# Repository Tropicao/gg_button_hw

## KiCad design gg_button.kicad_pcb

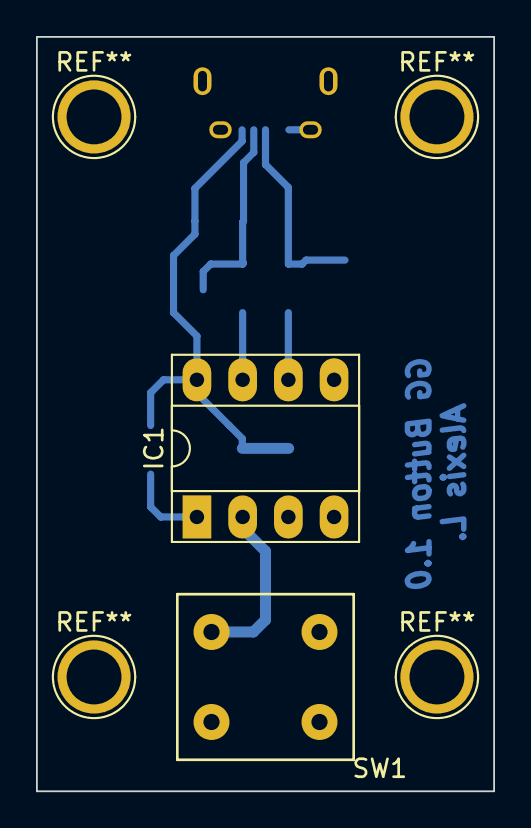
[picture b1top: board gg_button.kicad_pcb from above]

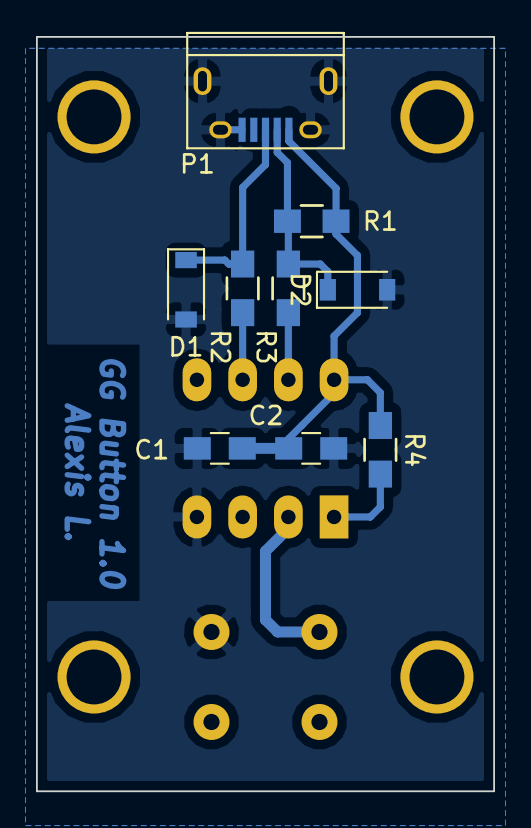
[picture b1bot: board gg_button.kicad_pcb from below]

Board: 2 copper layers, 25.4 x 41.9 mm, 11 parts (9 on the bottom side), 8 nets.

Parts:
C1: 10uF; C_0805_HandSoldering
C2: 0.1uF; C_0805_HandSoldering
D1, D2: 3V6; D_SOD-123
IC1: ATTINY45-P; DIP-8_W7.62mm_Socket_LongPads
P1: USB_OTG; USB_Micro-B
R1: 2k2; R_0805_HandSoldering
R2, R3: 68; R_0805_HandSoldering
R4: 4k7; R_0805_HandSoldering
SW1: SW_DPST; PVA1-SW

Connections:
/5V: C1.1, C2.1, IC1.8, P1.1, R1.1, R4.2
/D+: D1.1, P1.3, R2.2
/D-: D2.1, P1.2, R1.2, R3.2
/GND: C1.2, C2.2, D1.2, D2.2, IC1.4, P1.5, P1.6, SW1.2
unnamed: IC1.1, R4.1
unnamed: IC1.2, SW1.1
unnamed: IC1.6, R2.1
unnamed: IC1.7, R3.1
